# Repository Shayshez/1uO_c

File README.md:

1u Version (Pulp Logic) of Ornament & Crime, 30HP.

For pcb's and panels: https://pushermanproductions.com/product/plum-audio-1u-ornament-crime-pcb-and-aluminium-panel/

Teensy Assembling (with Supervisor):https://youtu.be/IDsQhNgkL-Y

OLED Screen Assembling: https://youtu.be/ywh_6SPNrSg 

Need help?
Join "Plum Audio DIY first aid" Group:
https://www.facebook.com/groups/PlumAudioDIY

Looking for assembled module?
https://www.plum-audio.com/product-page/1uo-c

** Note for Pusherman v1.1 Pcb's - There is minor silk screen mistake - The Inputs and Outputs not numberd correctly.

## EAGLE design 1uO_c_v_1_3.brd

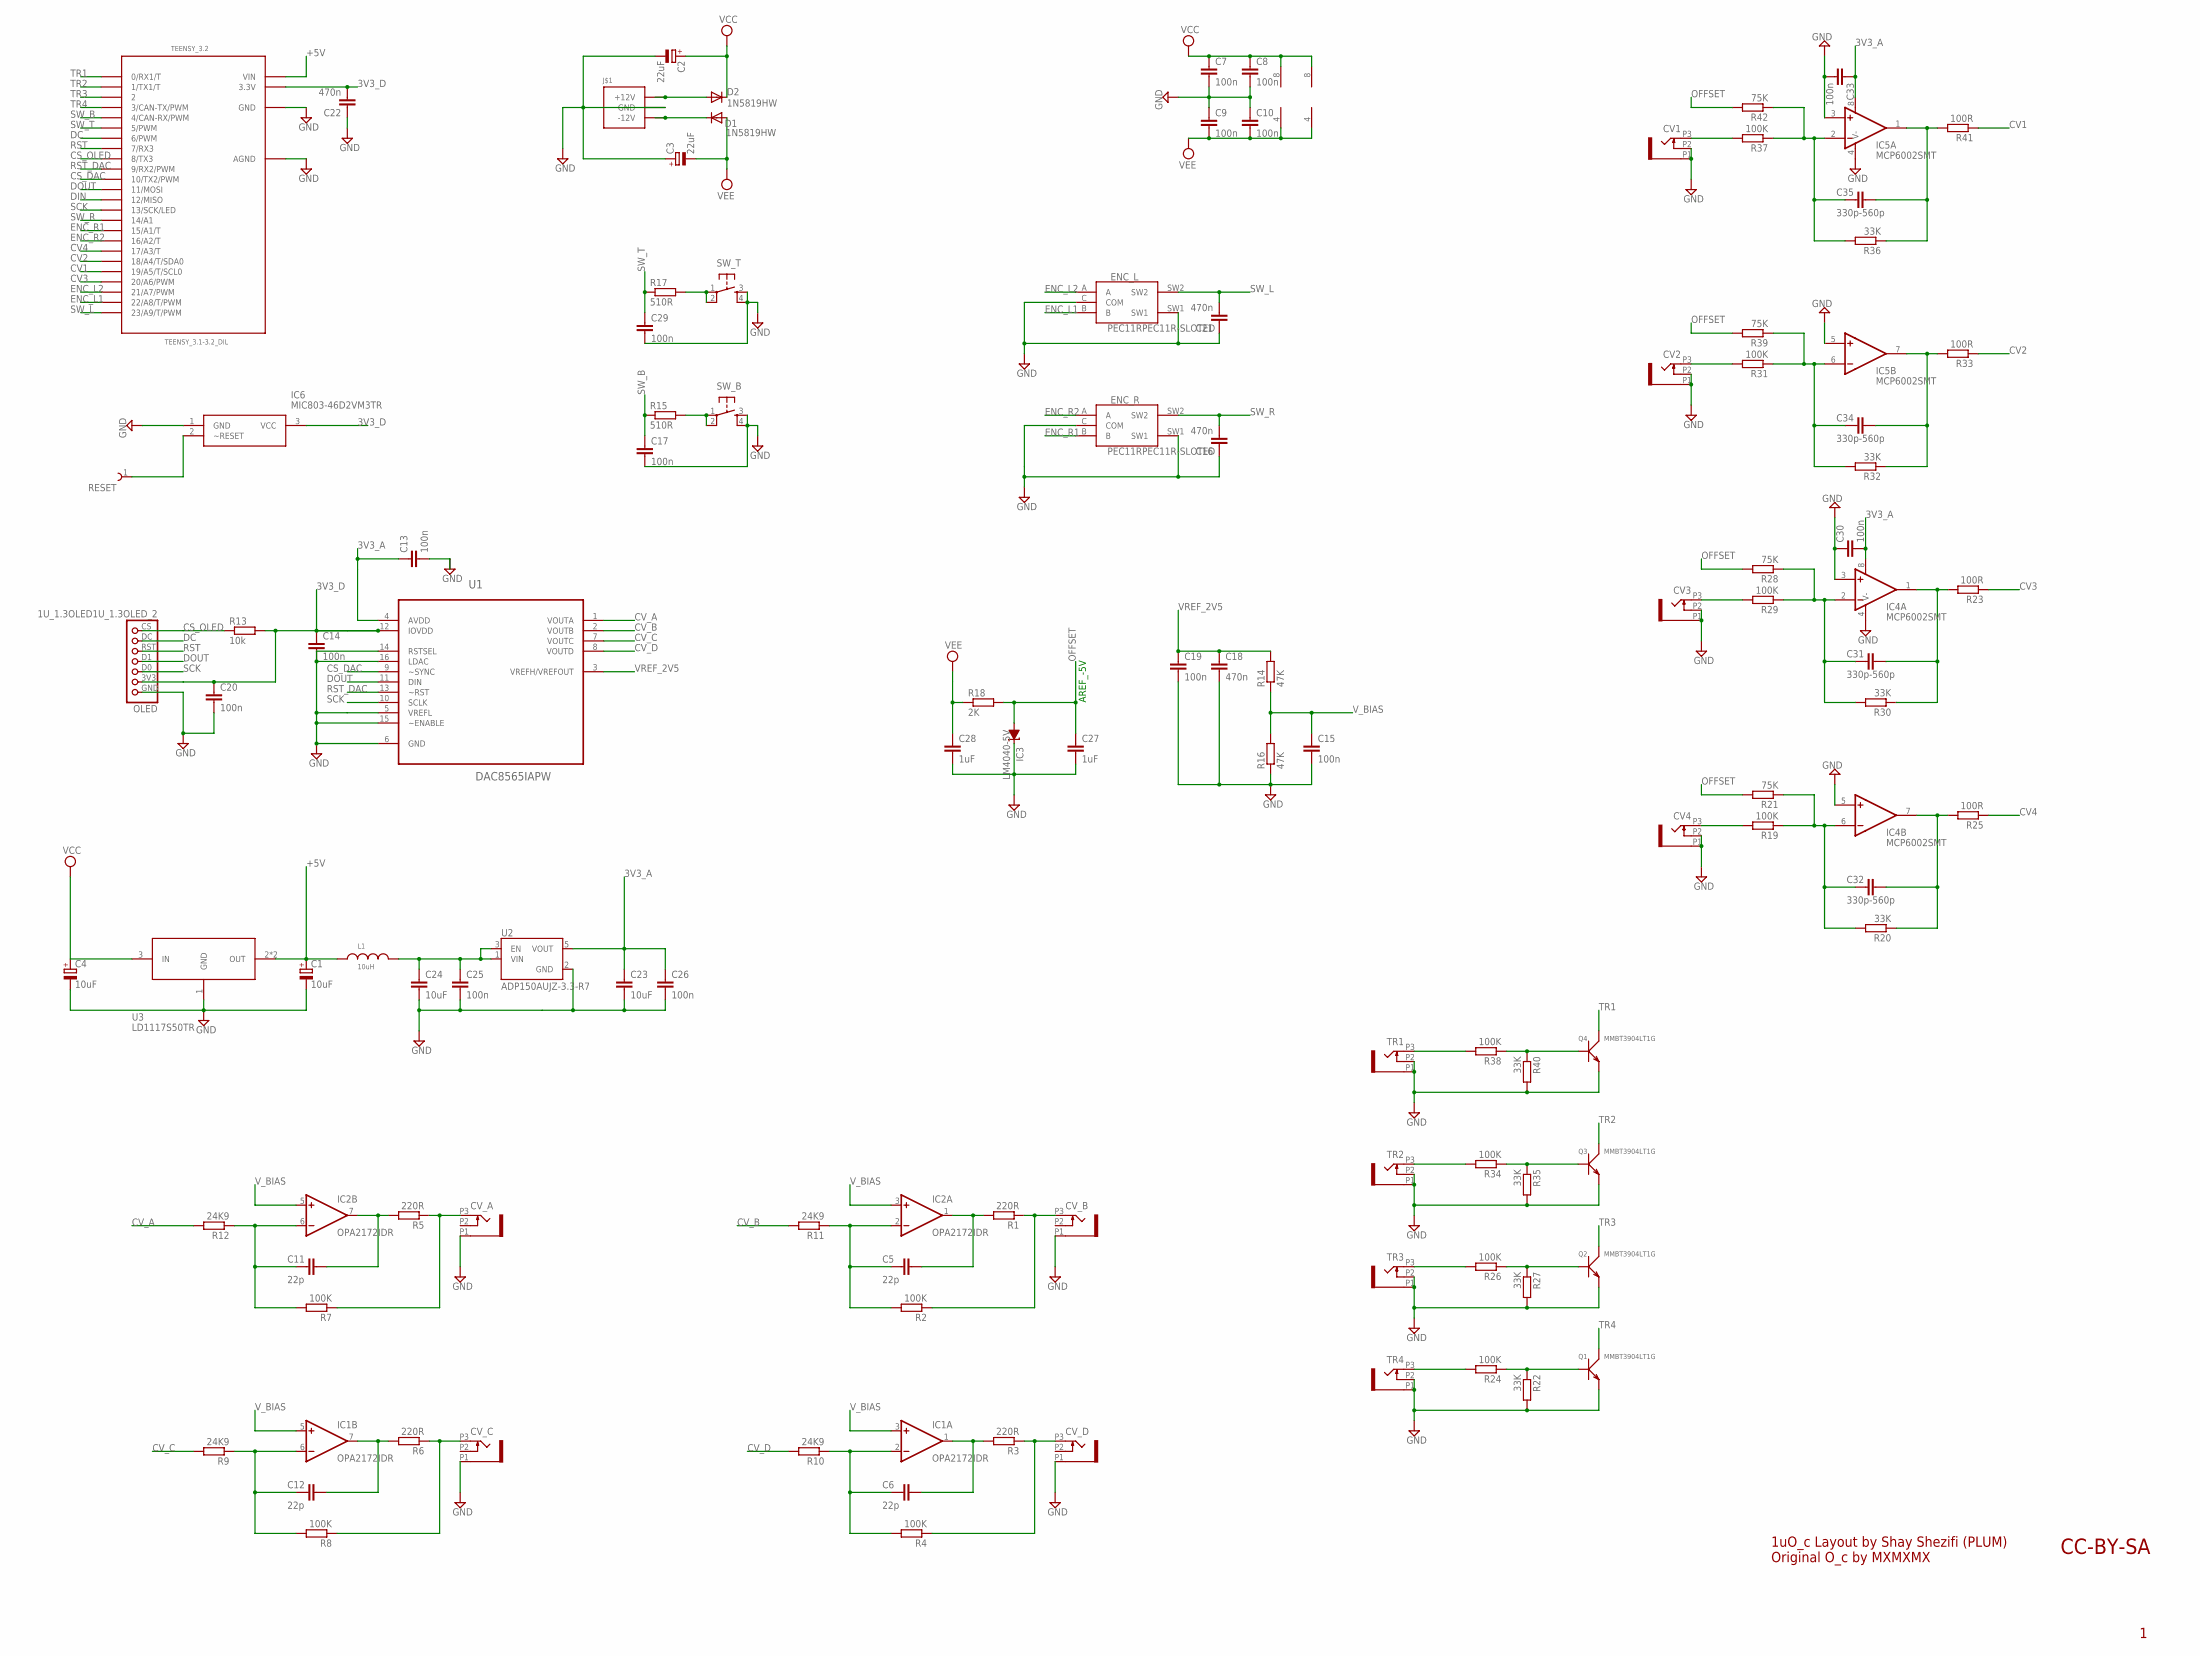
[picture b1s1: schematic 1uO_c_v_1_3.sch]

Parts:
C1, C4: 10uF; PANASONIC_B
C2, C3: 22uF; PANASONIC_C
C5, C6, C11, C12: 22p; C0603
C7, C8, C9, C10, C13, C14, C15, C17, C19, C20, C25, C26, C29, C30, C33: 100n; C0603
C16, C18, C21, C22: 470n; C0603
C23, C24: 10uF; C1206K
C27, C28: 1uF; C0603
C31, C32, C34, C35: 330p-560p; C0603
CV1, CV2, CV3, CV4: OG-PJ301_PJ301_THONKICONN; OG-PJ301_WQP_PJ_301M6_NO_HOLE
CV_A: OG-PJ301_PJ301_THONKICONN; OG-PJ301_WQP_PJ_301M6_NO_HOLE
CV_B: OG-PJ301_PJ301_THONKICONN; OG-PJ301_WQP_PJ_301M6_NO_HOLE
CV_C: OG-PJ301_PJ301_THONKICONN; OG-PJ301_WQP_PJ_301M6_NO_HOLE
CV_D: OG-PJ301_PJ301_THONKICONN; OG-PJ301_WQP_PJ_301M6_NO_HOLE
D1, D2: 1N5819HW; DIODE_SOD123
ENC_L: PEC11RPEC11R-SLOTED; PEC11R-SLOTED
ENC_R: PEC11RPEC11R-SLOTED; PEC11R-SLOTED
IC1, IC2: OPA2172IDR; SO08
IC3: LM4040-5V; DBZ_R-PDSO-G3
IC4, IC5: MCP6002SMT; SOIC8
IC6: MIC803-46D2VM3TR; SOT95P230X110-3N
J$1: POWER_SIMPLE10; POWER_10
L1: 10uH; WE-LQ_M
OLED: 1U_1.3OLED1U_1.3OLED_2; 1U_1.3OLED_2
Q1, Q2, Q3, Q4: MMBT3904LT1G; SOT-23
R1, R3, R5, R6: 220R; R0603
R2, R4, R7, R8, R19, R24, R26, R29, R31, R34, R37, R38: 100K; R0603
R9, R10, R11, R12: 24K9; R0603
R13: 10k; R0603
R14, R16: 47K; R0603
R15, R17: 510R; R0603
R18: 2K; R0603
R20, R22, R27, R30, R32, R35, R36, R40: 33K; R0603
R21, R28, R39, R42: 75K; R0603
R23, R25, R33, R41: 100R; R0603
RESET: 61300111121
SW_B: TAC_SWITCHPTH; TACTILE-PTH
SW_T: TAC_SWITCHPTH; TACTILE-PTH
TEENSY_3.2: TEENSY_3.1-3.2_DIL; TEENSY_3.0-3.2&LC_DIL
TR1, TR2, TR3, TR4: OG-PJ301_PJ301_THONKICONN; OG-PJ301_WQP_PJ_301M6_NO_HOLE
U1: DAC8565IAPW; SOP65P640X120-16N
U2: ADP150AUJZ-3.3-R7; SOT95P280X100-5N
U3: LD1117S50TR; SOT223

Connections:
3V3_A: C13.1, C23.1, C26.1, C30.2, C33.1, IC4.8 (V+), IC5.8 (V+), U1.4 (AVDD), U2.5 (VOUT)
3V3_D: C14.1, C20.1, C22.2, IC6.3 (VCC), OLED.3V3, R13.2, TEENSY_3.2.3.3V, U1.12 (IOVDD)
+5V: C1.+, L1.1, TEENSY_3.2.VIN, U3.2 (OUT), U3.4 (OUT)
CS_DAC: TEENSY_3.2.10 (10/TX2/PWM), U1.9 (~SYNC)
CS_OLED: OLED.CS, R13.1, TEENSY_3.2.8 (8/TX3)
CV1: R41.1, TEENSY_3.2.19/A5 (19/A5/T/SCL0)
CV2: R33.1, TEENSY_3.2.18/A4 (18/A4/T/SDA0)
CV3: R23.1, TEENSY_3.2.20/A6 (20/A6/PWM)
CV4: R25.1, TEENSY_3.2.17/A3 (17/A3/T)
CV_A: R12.2, U1.1 (VOUTA)
CV_B: R11.2, U1.2 (VOUTB)
CV_C: R9.2, U1.7 (VOUTC)
CV_D: R10.2, U1.8 (VOUTD)
DC: OLED.DC, TEENSY_3.2.6 (6/PWM)
DIN: TEENSY_3.2.12 (12/MISO)
DOUT: OLED.D1, TEENSY_3.2.11 (11/MOSI), U1.11 (DIN)
ENC_L1: ENC_L.B, TEENSY_3.2.22/A8 (22/A8/T/PWM)
ENC_L2: ENC_L.A, TEENSY_3.2.21/A7 (21/A7/PWM)
ENC_R1: ENC_R.B, TEENSY_3.2.15/A1 (15/A1/T)
ENC_R2: ENC_R.A, TEENSY_3.2.16/A2 (16/A2/T)
GND: C1.-, C2.-, C3.+, C4.-, C7.2, C8.2, C9.1, C10.1, C13.2, C14.2, C15.2, C16.1, C17.2, C18.2, C19.2, C20.2, C21.1, C22.1, C23.2, C24.2, C25.2, C26.2, C27.2, C28.2, C29.2, C30.1, C33.2, CV1.P1 (1), CV1.P2 (2), CV2.P1 (1), CV2.P2 (2), CV3.P1 (1), CV3.P2 (2), CV4.P1 (1), CV4.P2 (2), CV_A.P1 (1), CV_B.P1 (1), CV_C.P1 (1), CV_D.P1 (1), ENC_L.C (COM), ENC_L.SW1, ENC_R.C (COM), ENC_R.SW1, IC3.1 (C), IC4.3 (+IN), IC4.4 (V-), IC4.5 (+IN), IC5.3 (+IN), IC5.4 (V-), IC5.5 (+IN), IC6.1 (GND), J$1.3 (GND), J$1.4 (GND), J$1.5 (GND), J$1.6 (GND), J$1.7 (GND), J$1.8 (GND), OLED.GND, Q1.2 (E), Q2.2 (E), Q3.2 (E), Q4.2 (E), R16.1, R22.2, R27.2, R35.2, R40.2, SW_B.3, SW_B.4, SW_T.3, SW_T.4, TEENSY_3.2.AGND, TEENSY_3.2.GND, TR1.P1 (1), TR1.P2 (2), TR2.P1 (1), TR2.P2 (2), TR3.P1 (1), TR3.P2 (2), TR4.P1 (1), TR4.P2 (2), U1.5 (VREFL), U1.6 (GND), U1.14 (RSTSEL), U1.15 (~ENABLE), U1.16 (LDAC), U2.2 (GND), U3.1 (GND)
unnamed: D1.C, J$1.1 (-12V), J$1.2 (-12V)
unnamed: D2.A, J$1.9 (+12V), J$1.10 (+12V)
unnamed: C24.1, C25.1, L1.2, U2.1 (VIN), U2.3 (EN)
unnamed: CV1.P3 (3), R37.2
unnamed: C35.2, IC5.2 (-IN), R36.2, R37.1, R42.1
unnamed: C35.1, IC5.1 (OUT), R36.1, R41.2
unnamed: R17.2, SW_T.1, SW_T.2
unnamed: CV2.P3 (3), R31.2
unnamed: R15.2, SW_B.1, SW_B.2
unnamed: C34.2, IC5.6 (-IN), R31.1, R32.2, R39.1
unnamed: C34.1, IC5.7 (OUT), R32.1, R33.2
unnamed: CV3.P3 (3), R29.2
unnamed: C31.2, IC4.2 (-IN), R28.1, R29.1, R30.2
unnamed: C31.1, IC4.1 (OUT), R23.2, R30.1
unnamed: CV4.P3 (3), R19.2
unnamed: C32.2, IC4.6 (-IN), R19.1, R20.2, R21.1
unnamed: C32.1, IC4.7 (OUT), R20.1, R25.2
unnamed: R38.2, TR1.P3 (3)
unnamed: Q4.1 (B), R38.1, R40.1
unnamed: R34.2, TR2.P3 (3)
unnamed: Q3.1 (B), R34.1, R35.1
unnamed: R26.2, TR3.P3 (3)
unnamed: Q2.1 (B), R26.1, R27.1
unnamed: R24.2, TR4.P3 (3)
unnamed: Q1.1 (B), R22.1, R24.1
unnamed: C5.2, IC2.2 (-IN), R2.2, R11.1
unnamed: C11.2, IC2.6 (-IN), R7.2, R12.1
unnamed: C11.1, IC2.7 (OUT), R5.2
unnamed: CV_A.P3 (3), R5.1, R7.1
unnamed: C5.1, IC2.1 (OUT), R1.2
unnamed: CV_B.P3 (3), R1.1, R2.1
unnamed: C12.2, IC1.6 (-IN), R8.2, R9.1
unnamed: C12.1, IC1.7 (OUT), R6.2
unnamed: CV_C.P3 (3), R6.1, R8.1
unnamed: C6.2, IC1.2 (-IN), R4.2, R10.1
unnamed: C6.1, IC1.1 (OUT), R3.2
unnamed: CV_D.P3 (3), R3.1, R4.1
unnamed: IC6.2 (~RESET), RESET.1
OFFSET: C27.1, IC3.2 (A), R18.2, R21.2, R28.2, R39.2, R42.2
RST: OLED.RST, TEENSY_3.2.7 (7/RX3)
RST_DAC: TEENSY_3.2.9 (9/RX2/PWM), U1.13 (~RST)
SCK: OLED.D0, TEENSY_3.2.13 (13/SCK/LED), U1.10 (SCLK)
SW_B: C17.1, R15.1, TEENSY_3.2.4 (4/CAN-RX/PWM)
SW_L: C21.2, ENC_L.SW2, TEENSY_3.2.23/A9 (23/A9/T/PWM)
SW_R: C16.2, ENC_R.SW2, TEENSY_3.2.14/A0 (14/A1)
SW_T: C29.1, R17.1, TEENSY_3.2.5 (5/PWM)
TR1: Q4.3 (C), TEENSY_3.2.0 (0/RX1/T)
TR2: Q3.3 (C), TEENSY_3.2.1 (1/TX1/T)
TR3: Q2.3 (C), TEENSY_3.2.2
TR4: Q1.3 (C), TEENSY_3.2.3 (3/CAN-TX/PWM)
VCC: C2.+, C4.+, C7.1, C8.1, D2.C, IC1.8 (V+), IC2.8 (V+), U3.3 (IN)
VEE: C3.-, C9.2, C10.2, C28.1, D1.A, IC1.4 (V-), IC2.4 (V-), R18.1
VREF_2V5: C18.1, C19.1, R14.2, U1.3 (VREFH/VREFOUT)
V_BIAS: C15.1, IC1.3 (+IN), IC1.5 (+IN), IC2.3 (+IN), IC2.5 (+IN), R14.1, R16.2

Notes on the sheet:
AREF_-5V
1uO_c Layout by Shay Shezifi (PLUM) Original O_c by MXMXMX
CC-BY-SA

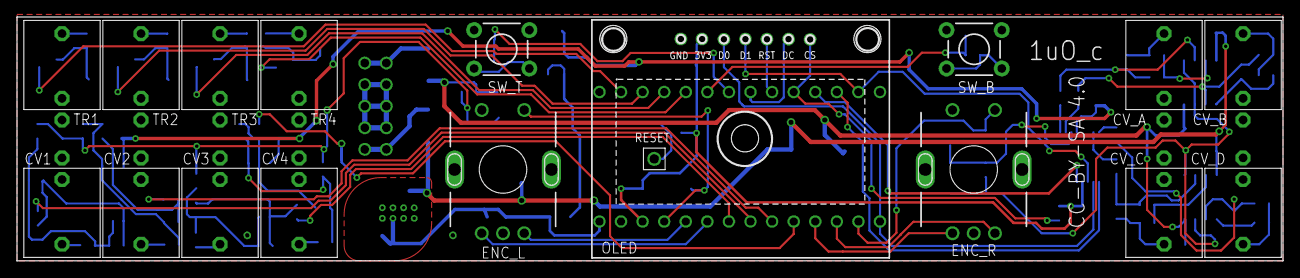
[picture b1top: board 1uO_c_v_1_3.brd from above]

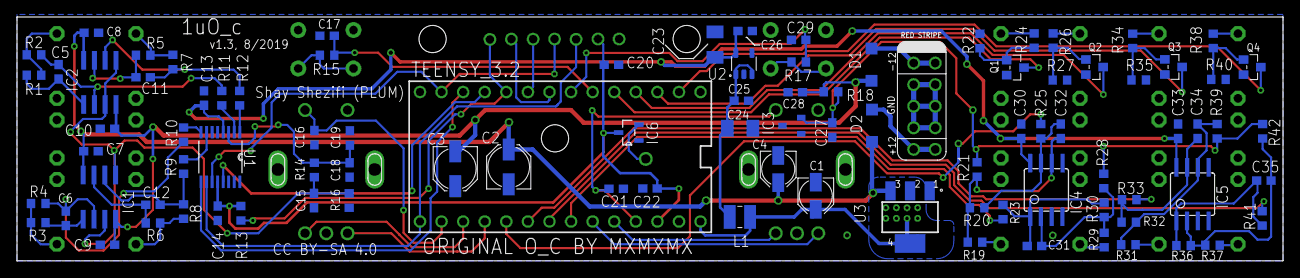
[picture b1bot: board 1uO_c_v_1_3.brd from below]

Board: 2 copper layers, 149.0 x 28.7 mm, 113 parts (95 on the bottom side), 74 nets.

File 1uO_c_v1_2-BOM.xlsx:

| Mouser Project: | https://www.mouser.com/ProjectManager/ProjectDetail.aspx?Acc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
Qty | Value | Device | Package | Parts | Mouser | Description | ALLIED_NUMBER | ALLIED_PRICE-STOCK | ARROW_PART_NUMBER | ARROW_PRICE-STOCK | AVAILABILITY | DESCRIPTION | HEIGHT | MANUFACTURER_NAME | MANUFACTURER_PART_NUMBER | MF | MP | MPN | PACKAGE | PRICE | RS_PART_NUMBER | RS_PRICE-STOCK | SPICEPREFIX | VALUE | WE-NUMBER
4 | 100R | R-EU_R0603 | R0603 | R23, R25, R33, R41 | 603-RC0603FR-07100RL | RESISTOR, European symbol |  |  |  |  |  |  |  |  |  |  |  |  |  |  |  |  | R
4 | 220R | R-EU_R0603 | R0603 | R1, R3, R5, R6 | 603-RC0603FR-07220RL | RESISTOR, European symbol |  |  |  |  |  |  |  |  |  |  |  |  |  |  |  |  | R
2 | 510R | R-EU_R0603 | R0603 | R15, R17 | 603-RC0603FR-07510RL | RESISTOR, European symbol |  |  |  |  |  |  |  |  |  |  |  |  |  |  |  |  | R
1 | 2K | R-EU_R0603 | R0603 | R18 | 603-RC0603FR-102KL | RESISTOR, European symbol |  |  |  |  |  |  |  |  |  |  |  |  |  |  |  |  | R
1 | 10k | R-EU_R0603 | R0603 | R13 | 603-RC0603FR-0710KL | RESISTOR, European symbol |  |  |  |  |  |  |  |  |  |  |  |  |  |  |  |  | R
4 | 24K9 | R-EU_R0603 | R0603 | R9, R10, R11, R12 | 603-RC0603FR-0724K9L | RESISTOR, European symbol |  |  |  |  |  |  |  |  |  |  |  |  |  |  |  |  | R
8 | 33K | R-EU_R0603 | R0603 | R20, R22, R27, R30, R32, R35, R36, R40 | 603-RC0603FR-1333KL | RESISTOR, European symbol |  |  |  |  |  |  |  |  |  |  |  |  |  |  |  |  | R
2 | 47K | R-EU_R0603 | R0603 | R14, R16 | 603-RC0603FR-0747KL | RESISTOR, European symbol |  |  |  |  |  |  |  |  |  |  |  |  |  |  |  |  | R
4 | 75K | R-EU_R0603 | R0603 | R21, R28, R39, R42 | 603-AC0603FR-0775KL | RESISTOR, European symbol |  |  |  |  |  |  |  |  |  |  |  |  |  |  |  |  | R
12 | 100K | R-EU_R0603 | R0603 | R2, R4, R7, R8, R19, R24, R26, R29, R31, R34, R37, R38 | 603-RC0603FR-07100KL | RESISTOR, European symbol |  |  |  |  |  |  |  |  |  |  |  |  |  |  |  |  | R
4 | 18p - 22p | C-EUC0603 C0G/NP0 | C0603 | C5, C6, C11, C12 | 80-C0603C220J5G7411 | CAPACITOR, European symbol
4 | 330p-560p | C-EUC0603 C0G/NP0 | C0603 | C31, C32, C34, C35 | 581-06035A561G | CAPACITOR, European symbol
15 | 100n | C-EUC0603 | C0603 | C7, C8, C9, C10, C13, C14, C15, C17, C19, C20, C25, C26, C29, C30, C33 | 80-C0603C104K3NAUTO | CAPACITOR, European symbol
4 | 470n | C-EUC0603 | C0603 | C16, C18, C21, C22 | 963-UMK107B7474KA-TR | CAPACITOR, European symbol
2 | 1uF | C-EUC0603 | C0603 | C27, C28 | 603-CC603KRX5R8BB105 | CAPACITOR, European symbol
2 | 10uF | C-EUC1206K | C1206K | C23, C24 | 963-TMK316BJ106ML-T | CAPACITOR, European symbol
2 | 10uF | CPOL-EUB | PANASONIC_B | C1, C4 | 667-EEE-FK1H100SR | POLARIZED CAPACITOR, European symbol |  |  |  |  |  |  |  |  |  |  |  |  |  |  |  |  | C
2 | 22uF | CPOL-EUC | PANASONIC_C | C2, C3 | 667-EEE-FK1H220SR | POLARIZED CAPACITOR, European symbol |  |  |  |  |  |  |  |  |  |  |  |  |  |  |  |  | C
1 | 10uH | WE-LQ_1210_744032001 | WE-LQ_M | L1 | 963-LB3218T100K | SMD Inductor |  |  |  |  |  |  |  |  |  |  |  |  |  |  |  |  |  |  | 744032001/1uH
2 | 1N5819HW | DIODE_DIODE-SOD123 | DIODE_SOD123 | D1, D2 | 621-1N5819HW-F | DIODE
4 | MMBT3904LT1G | SMD-TRANSISTORS-NPN-40V-200MA-MMBT3904LT1G(SOT-23) | SOT-23 | Q1, Q2, Q3, Q4 | 863-MMBT3904LT1G | 305010013 |  |  |  |  |  |  |  |  |  |  |  | MMBT3904LT1G |  |  |  |  |  | MMBT3904LT1G
1 | DAC8565IAPW | DAC8565IAPW | SOP65P640X120-16N | U1 | 595-DAC8565IAPW | Quad Channel DAC |  |  |  |  | Good | 16-Bit, Quad Channel, Ultra-Low Glitch, Voltage Output DAC with 2.5V, 2ppm/C In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 |  |  |  | Texas Instruments | DAC8565IAPW |  | TSSOP-16 Texas Instruments | 10.78 USD
1 | LM4040-5V | LM4041B12DBZ | DBZ_R-PDSO-G3 | IC3 | 926-LM4040DIM350NOPB | PRECISION MICROPOWER SHUNT VOLTAGE REFERENCE
2 | TL072D | TL072D | SO08 | IC1, IC2 | 595-TL072CDR | OP AMP
2 | MCP6002SMT | MCP6002SMT | SOIC8 | IC4, IC5 | 579-MCP6002T-I/SN | Dual General Op Amp
1 | LD1117S50TR | LD1117S50TR | SOT223 | U3 | 511-LD1117S50 | http://octopart.com/ld1117s50tr-stmicroelectronics-529395 |  |  |  |  | Good | LD1117 Series 1300 mA 5 V Fixed Output Positive Voltage LDO Regulator - SOT-223 |  |  |  | STMicroelectronics | LD1117S50TR |  | SOT-223 STMicroelectronics | 0.19 USD
1 | MIC803-46D2VM3TR | MIC803-46D2VM3TR | SEE DESCRIPOTION -->> | IC6 | 998-MIC803-26D2VM3TR | Teensy Supervisor, You need this only if your case used Linear PSU, Use TH resi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 |  |  | MIC803-46D2VM3TR |  |  | 3-pin Microprocessor Supervosor Circui | mm | Micrel | MIC803-46D2VM3TR
1 | ADP150AUJZ-3.3-R7 | ADP150AUJZ-3.3-R7 | SOT95P280X100-5N | U2 | 584-ADP150AUJZ-3.3R7 | IC REG LINEAR 2V 150MA 5TSOT |  |  |  |  | Good | LDO Regulator Pos 2V 0.15A 5-Pin TSOT T/R |  |  |  | Analog Devices | ADP150AUJZ-2.0-R7 |  | TSOT-23 Analog Devices | 0.65 USD
1 | 1X40 Pin Header | Theensy / OLED connector
1 | 2X5 Pin Header | POWER | POWER_10 | J1 | J1
2 | Tact Switch | TACT_SWITCHPTH | TACTILE-PTH | SW1, SW2 | 612-TL1105SP-250 | Momentary Switch
2 | Tact Switch caps |  |  | SW1, SW2 | 12-1R-BK | For more colours: https://www.mouser.com/Search/Refine.aspx?FS=TRUE&N=0+4294759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
1 | TEENSY 3.2 | TEENSY_3.2 | TEENSY_3.2 | TEENSY_3.2 |  | https://store.oshpark.com/products/teensy-3-1
1 | OLED | 1U_1.3_OLED | 1U_1.3_OLED | See GitHub link -->> |  | https://github.com/Shayshez/1_3_OLED_FOR_1U
12 | THONKICONN | PJ301_PJ301_THONKICONN | PJ301_WQP_PJ_301M6 | CV1, CV2, CV3, CV4, CV_A, CV_B, CV_C, CV_D, TR1, TR2, TR3, TR4 | Thonk
2 | Encoder | PEC11R | PEC11R-4XXXK-SXXXX | ENC_L, ENC_R | 858-EN11-HSM1BF20 | Incremental encoder 24 detents 24 pulses Bourns 24 Pulse Incremental Mechanical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 | 70407906 | https://www.alliedelec.com/bourns-pec11r-4215k-s0024/70407906/ | PEC11R-4215K-S0024 | http://uk.rs-online.com/web/p/products/1674651 |  | Incremental encoder 24 detents 24 pulses Bourns 24 Pulse Incremental Mechanical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 | mm | Bourns | PEC11R-4215K-S0024 |  |  |  |  |  | 1674651 | http://uk.rs-online.com/web/p/products/1674651
2 | Knobs | Sifam soft touch Encoder Knob |  |  | Thonk | https://www.thonk.co.uk/shop/sifam-soft-touch-encoder-knobs/
3 | 3M/6MM Nylon standoffs | For screen mounting |  |  |  | https://www.aliexpress.com/item/100pcs-lot-M3-5-6-8-10-12-15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
5 | 3M Nylon screws | For screen mounting |  |  |  | https://www.aliexpress.com/item/Black-100Pcs-Lot-Plastic-Nyl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

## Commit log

2018-10-13 1uO_c
2019-07-21 Add files via upload
    Mouser Project added

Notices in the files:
1uO_c_v_1_3.brd:
CC BY-SA 4.0
parts and their libraries:
Wurth_Elektronik_Passive_rev17b: Copyright: Würth Elektronik
